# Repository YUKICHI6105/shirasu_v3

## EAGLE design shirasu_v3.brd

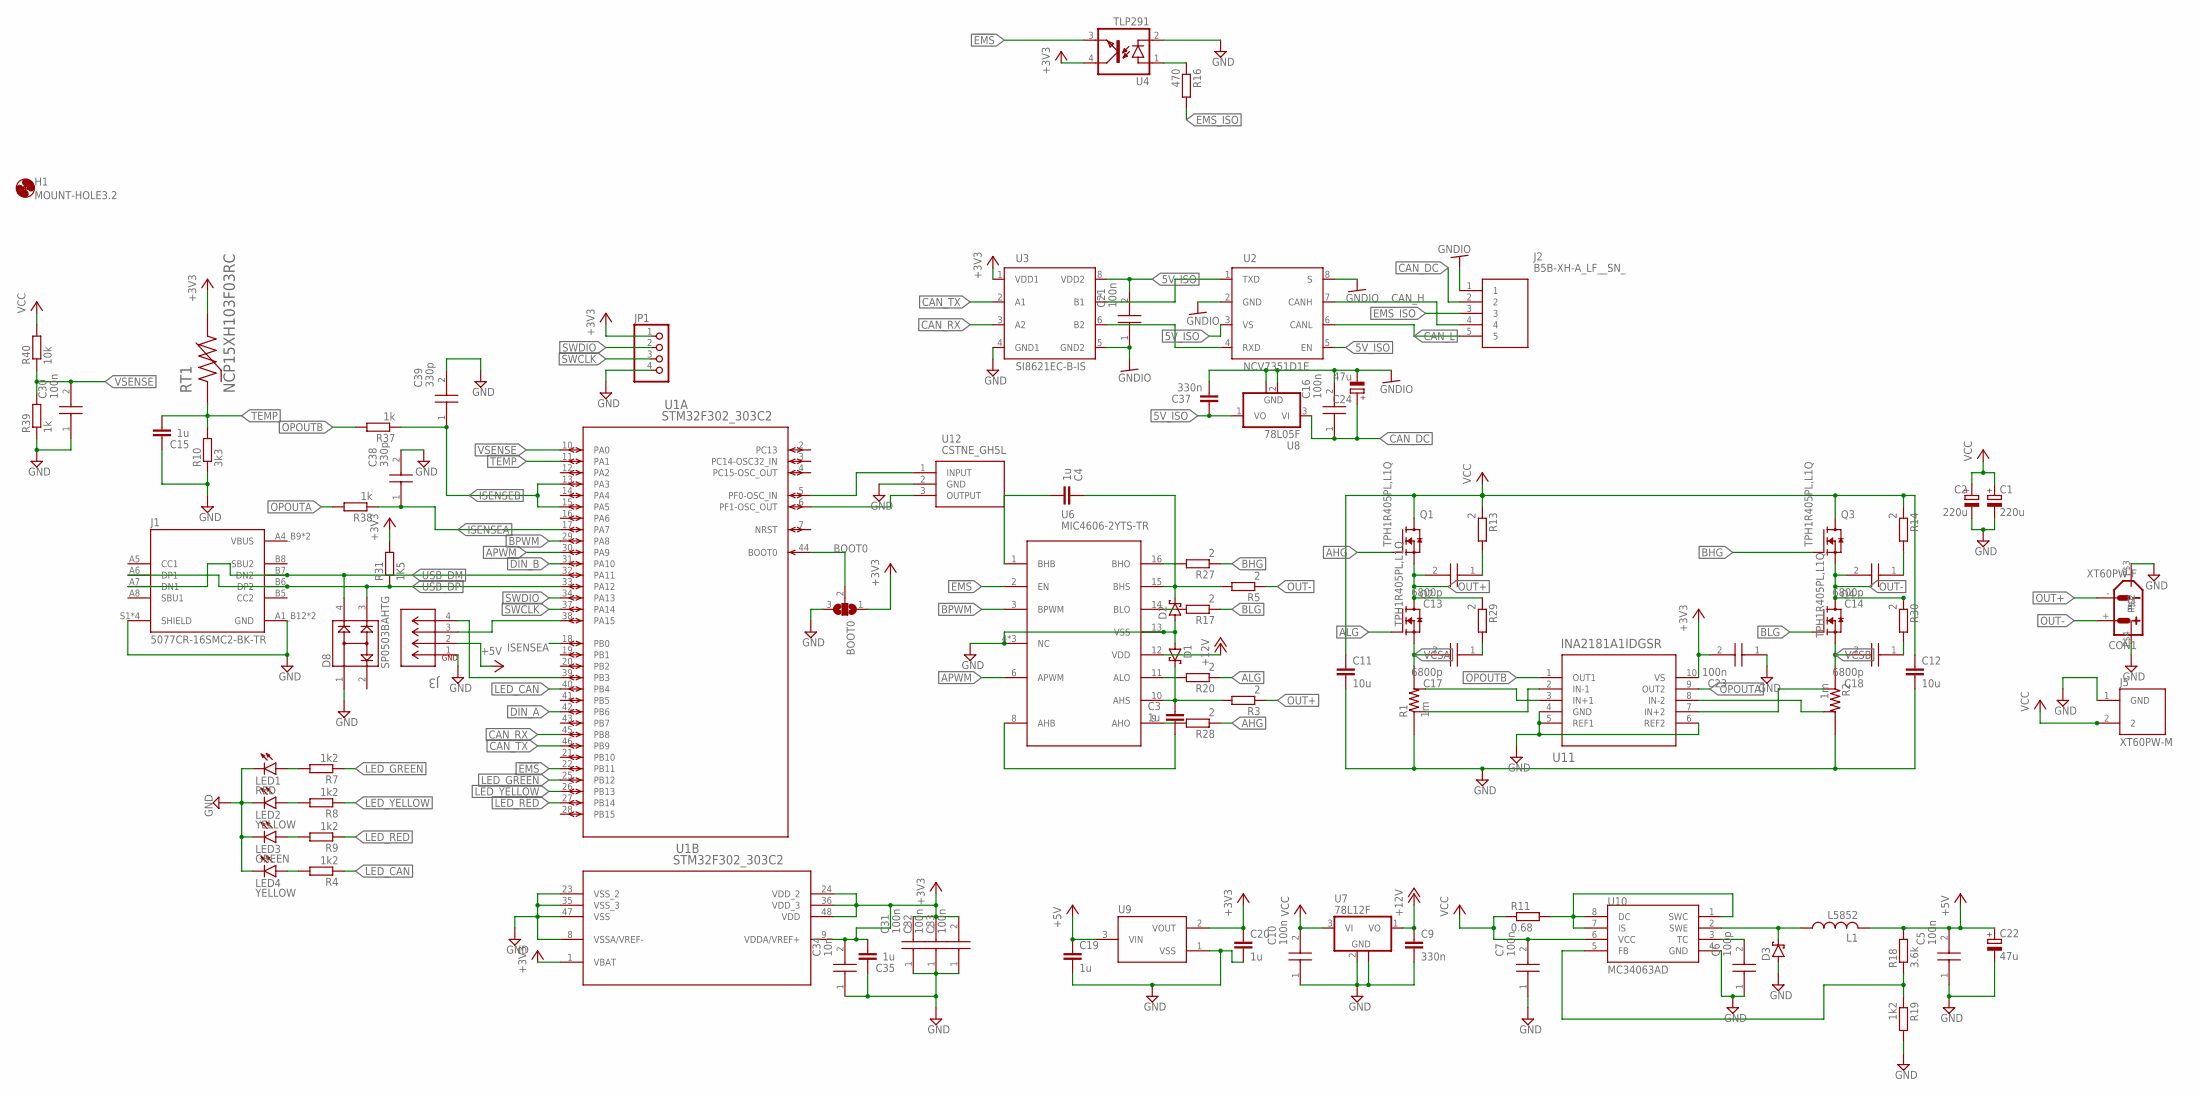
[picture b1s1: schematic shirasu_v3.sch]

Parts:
BOOT0: SJ2W; SJ_2
C1, C2: 220u; E5-10,5
C3, C4, C15, C19, C20, C35: 1u; C0603
C5, C7, C10, C16, C21, C23, C30, C31, C32, C33: 100n; CAPC1005X55N
C6: 100p; CAPC1005X55N
C9, C37: 330n; C0603
C11, C12: 10u; C0805
C13, C14, C17, C18: 6800p; CAPC1005X55N
C22, C24: 47u; E2,5-5
C34: 10n; CAPC1005X55N
C38, C39: 330p; CAPC1005X55N
CON1: XT60PW-F
D1, D2, D3: PMEG6010CEJ,115; SOD323_ST
D8: SP0503BAHTG; SOT143
H1: MOUNT-HOLE3.2; 3,2
J1: 5077CR-16SMC2-BK-TR; NELTRON_5077CR-16SMC2-BK-TR
J2: B5B-XH-A_LF__SN_; SHDR5W64P0X250_1X5_1490X575X70
J3: EP2.5-4-SIDE; CONN4_1744426-4
J5: XT60PW-M; AMASS_XT60PW-M
JP1: PINHD-1X4; 1X04
L1: L5852
LED1: RED; CHIP-LED0603
LED2, LED4: YELLOW; CHIP-LED0603
LED3: GREEN; CHIP-LED0603
Q1, Q2, Q3, Q4: TPH1R405PL,L1Q; SOPADVANCE
R1, R2: 1m; 2512-4PAD
R3, R5, R13, R14, R17, R20, R27, R28, R29, R30: 2; R0402
R4, R7, R8, R9, R19: 1k2; R0402
R10: 3k3; R0402
R11: 0.68; R1206
R16: 470; R0402
R18: 3.6k; R0603
R31: 1K5; R0402
R37, R38, R39: 1k; R0402
R40: 10k; R0402
RT1: NCP15XH103F03RC; THRMC1005X55N
U1: STM32F302_303C2; LQFP48-7X7MM
U2: NCV7351D1E; SO08
U3: SI8621EC-B-IS; SO08
U4: TLP291; MINI-FLAT-4
U6: MIC4606-2YTS-TR; TSSOP16
U7: 78L12F; SOT89
U8: 78L05F; SOT89
U9: XC6206; SOT95P240X110-3
U10: MC34063AD; SOIC8
U11: INA2181A1IDGSR; DGS10
U12: CSTNE_GH5L

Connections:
5V_ISO: C21.2, C37.1, U2.3 (VS), U2.5 (EN), U3.8 (VDD2), U8.1 (VO)
!EMS: U1.22 (PB11), U4.3 (EMIT), U6.2 (EN)
+3V3: BOOT0.1, C20.1, C23.2, C31.2, C32.2, C33.2, C34.2, C35.2, JP1.1, R31.2, RT1.2, U1.1 (VBAT), U1.9 (VDDA/VREF+), U1.24 (VDD_2), U1.36 (VDD_3), U1.48 (VDD), U3.1 (VDD1), U4.4 (COL), U9.2 (VOUT), U11.10 (VS)
+5V: C5.2, C19.1, C22.+, J3.2, L1.P$2 (2), R18.2, U9.3 (VIN)
+12V: C9.1, U6.12 (VDD), U7.1 (VO)
AHG: Q1.4 (G), R28.1
ALG: Q2.4 (G), R20.1
APWM: U1.30 (PA9), U6.6 (APWM)
BHG: Q3.4 (G), R27.1
BLG: Q4.4 (G), R17.1
BOOT0: BOOT0.2, U1.44 (BOOT0)
BPWM: U1.29 (PA8), U6.3 (BPWM)
CAN_DC: C16.1, C24.+, J2.2, U8.3 (VI)
CAN_H: J2.4, U2.7 (CANH)
CAN_L: J2.5, U2.6 (CANL)
CAN_RX: U1.45 (PB8), U3.3 (A2)
CAN_TX: U1.46 (PB9), U3.2 (A1)
DIN_A: U1.42 (PB6)
DIN_B: U1.31 (PA10)
EMS_ISO: J2.3, R16.2
ENC_A: J3.3, U1.38 (PA15)
ENC_B: J3.4, U1.39 (PB3)
GND: BOOT0.3, C1.-, C2.-, C5.1, C6.1, C7.1, C9.2, C10.1, C11.2, C12.2, C15.1, C19.2, C20.2, C22.-, C23.1, C30.1, C31.1, C32.1, C33.1, C34.1, C35.1, C38.2, C39.2, CON1.P$3, CON1.P$4, D1.A, D2.A, D3.A, D8.1, J1.A1_B12 (GND), J1.B1_A12 (GND), J1.S1 (SHIELD), J1.S2 (SHIELD), J1.S3 (SHIELD), J1.S4 (SHIELD), J3.1, J5.1 (GND), JP1.4, LED1.C, LED2.C, LED3.C, LED4.C, R1.1, R1.2 (1), R2.3 (2), R2.4 (2), R10.1, R19.2, R39.1, U1.8 (VSSA/VREF-), U1.23 (VSS_2), U1.35 (VSS_3), U1.47 (VSS), U3.4 (GND1), U4.2 (C), U6.4 (NC), U6.5 (NC), U6.7 (NC), U6.13 (VSS), U7.2 (GND), U7.2@1 (GND), U9.1 (VSS), U10.4 (GND), U11.4 (GND), U11.5 (REF1), U11.6 (REF2), U12.2 (GND)
GNDIO: C16.2, C21.1, C24.-, C37.2, J2.1, U2.2 (GND), U2.8 (S), U3.5 (GND2), U8.2 (GND), U8.2@1 (GND)
ISENSEA: C38.1, R38.1, U1.17 (PA7), U1.18 (PB0)
ISENSEB: C39.1, R37.1, U1.13 (PA3), U1.15 (PA5)
LED_CAN: R4.1, U1.40 (PB4)
LED_GREEN: R7.1, U1.25 (PB12)
LED_RED: R9.1, U1.27 (PB14)
LED_YELLOW: R8.1, U1.26 (PB13)
unnamed: C17.1, R29.2
unnamed: C18.1, R30.2
unnamed: R27.2, U6.16 (BHO)
unnamed: C4.1, D2.C, R5.2, U6.15 (BHS)
unnamed: C4.2, U6.1 (BHB)
unnamed: R17.2, U6.14 (BLO)
unnamed: R20.2, U6.11 (ALO)
unnamed: R28.2, U6.9 (AHO)
unnamed: C3.2, U6.8 (AHB)
unnamed: C3.1, D1.C, R3.2, U6.10 (AHS)
unnamed: LED1.A, R7.2
unnamed: LED2.A, R8.2
unnamed: LED3.A, R9.2
unnamed: LED4.A, R4.2
unnamed: U2.1 (TXD), U3.7 (B1)
unnamed: U2.4 (RXD), U3.6 (B2)
unnamed: C14.1, R14.2
unnamed: U1.6 (PF1-OSC_OUT), U12.3 (OUTPUT)
unnamed: C13.1, R13.2
unnamed: R1.6 (4), U11.3 (IN+1)
unnamed: R2.5 (3), U11.7 (IN+2)
unnamed: R16.1, U4.1 (A)
unnamed: D3.C, L1.P$1 (1), U10.2 (SWE)
unnamed: C6.2, U10.3 (TC)
unnamed: R18.1, R19.1, U10.5 (FB)
unnamed: R2.6 (4), U11.8 (IN-2)
unnamed: R11.2, U10.1 (SWC), U10.7 (IS), U10.8 (DC)
unnamed: R1.5 (3), U11.2 (IN-1)
unnamed: U1.5 (PF0-OSC_IN), U12.1 (INPUT)
OPOUTA: R38.2, U11.9 (OUT2)
OPOUTB: R37.2, U11.1 (OUT1)
OUT+: C13.2, CON1.-, Q1.1 (S), Q1.2 (S), Q1.3 (S), Q2.5 (D), Q2.6 (D), Q2.7 (D), Q2.8 (D), Q2.9 (D), R3.1, R29.1
OUT-: C14.2, CON1.+, Q3.1 (S), Q3.2 (S), Q3.3 (S), Q4.5 (D), Q4.6 (D), Q4.7 (D), Q4.8 (D), Q4.9 (D), R5.1, R30.1
SWCLK: JP1.3, U1.37 (PA14)
SWDIO: JP1.2, U1.34 (PA13)
TEMP: C15.2, R10.2, RT1.1, U1.11 (PA1)
USB_DM: D8.4, J1.A7 (DN1), J1.B7 (DN2), U1.32 (PA11)
USB_DP: D8.3, J1.A6 (DP1), J1.B6 (DP2), R31.1, U1.33 (PA12)
VBUS: J1.A4_B9 (VBUS), J1.B4_A9 (VBUS)
VCC: C1.+, C2.+, C7.2, C10.2, C11.1, C12.1, J5.2, Q1.5 (D), Q1.6 (D), Q1.7 (D), Q1.8 (D), Q1.9 (D), Q3.5 (D), Q3.6 (D), Q3.7 (D), Q3.8 (D), Q3.9 (D), R11.1, R13.1, R14.1, R40.2, U7.3 (VI), U10.6 (VCC)
VCSA: C17.2, Q2.1 (S), Q2.2 (S), Q2.3 (S), R1.3 (2), R1.4 (2)
VCSB: C18.2, Q4.1 (S), Q4.2 (S), Q4.3 (S), R2.1, R2.2 (1)
VSENSE: C30.2, R39.2, R40.1, U1.10 (PA0)

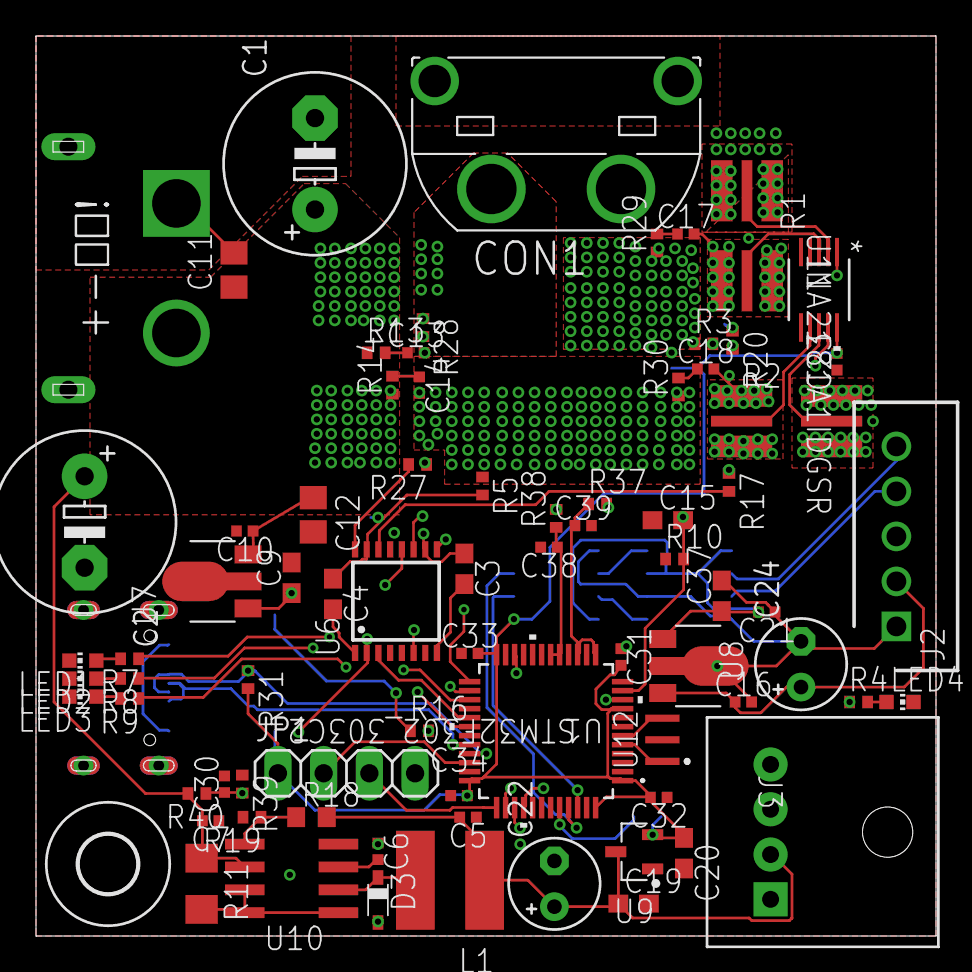
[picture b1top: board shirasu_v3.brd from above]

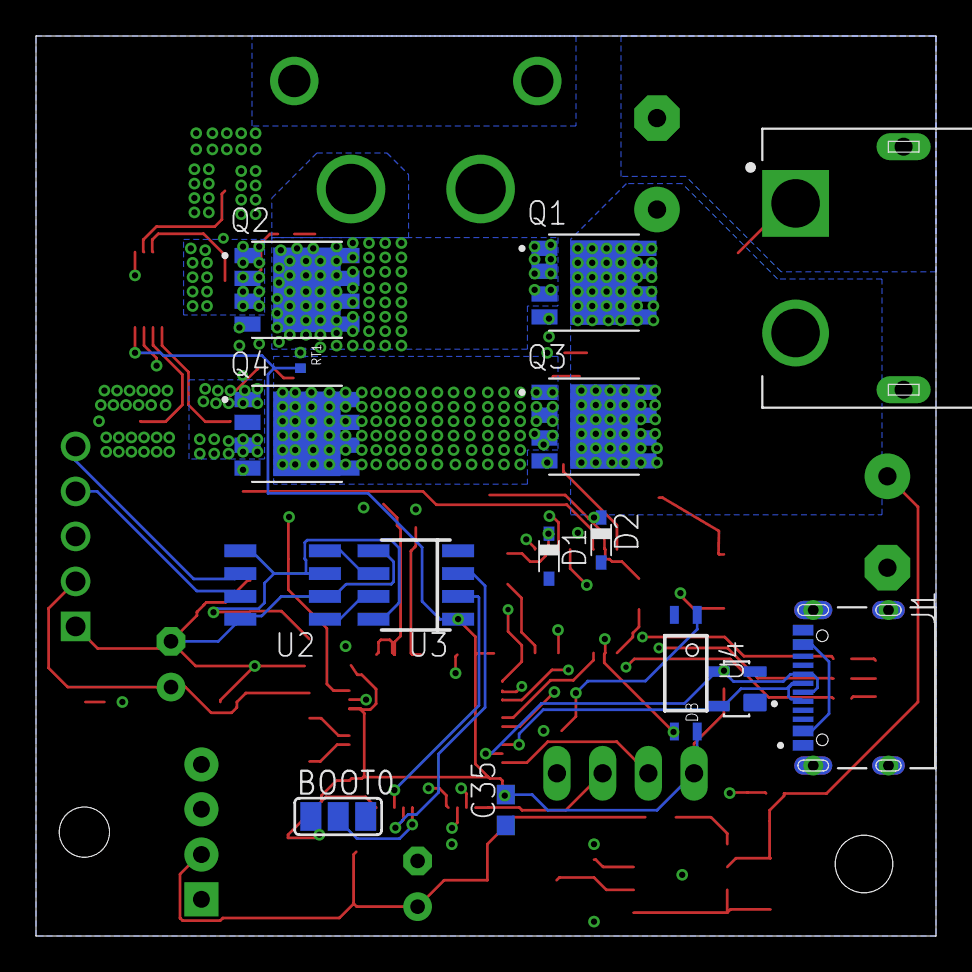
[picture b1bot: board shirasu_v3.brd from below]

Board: 4 copper layers, 50.0 x 50.0 mm, 91 parts (15 on the bottom side), 71 nets.

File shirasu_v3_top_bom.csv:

Comment,Designator,Footprint,LCSC Part #
0.68,R11,R1206,
1K5,R31,R0402,
1k,R37 R38 R39,R0402,
1k2,R4 R7 R8 R9 R19,R0402,
1m,R1 R2,2512-4PAD,
1u,C3 C4 C15 C19 C20,C0603,
2,R3 R5 R13 R14 R17 R20 R27 R28 R29 R30,R0402,
3.6k,R18,R0603,
3k3,R10,R0402,
10k,R40,R0402,
10n,C34,CAPC1005X55N,
10u,C11 C12,C0805,
78L05F,U8,SOT89,
78L12F,U7,SOT89,
100n,C5 C7 C10 C16 C21 C23 C30 C31 C32 C33,CAPC1005X55N,
100p,C6,CAPC1005X55N,
330n,C9 C37,C0603,
330p,C38 C39,CAPC1005X55N,
470,R16,R0402,
6800p,C13 C14 C17 C18,CAPC1005X55N,
CSTNE_GH5L,U12,CSTNE_GH5L,
GREEN,LED3,CHIP-LED0603,
INA2181A1IDGSR,U11,DGS10,
L5852,L1,L5852,
MC34063AD,U10,SOIC8,
MIC4606-2YTS-TR,U6,TSSOP16,
PMEG6010CEJ 115,D3,SOD323_ST,
RED,LED1,CHIP-LED0603,
STM32F302_303C2,U1,LQFP48-7X7MM,
XC6206,U9,SOT95P240X110-3,
YELLOW,LED2 LED4,CHIP-LED0603,

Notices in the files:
parts and their libraries:
COPYRIGHT: Copyright (C) 2016 Accelerated Designs. All rights reserved
COPYRIGHT: Copyright (C) 2018 Accelerated Designs. All rights reserved
